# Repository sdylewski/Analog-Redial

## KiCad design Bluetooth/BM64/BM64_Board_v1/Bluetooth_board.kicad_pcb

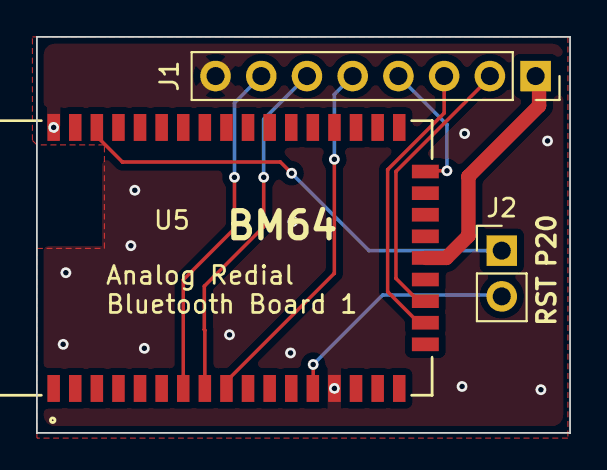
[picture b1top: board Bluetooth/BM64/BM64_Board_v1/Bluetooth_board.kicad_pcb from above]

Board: 2 copper layers, 29.6 x 22.0 mm, 3 parts (0 on the bottom side), 10 nets.

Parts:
J1: PINHD_1x8_Female; PinSocket_1x08_P2.54mm_Vertical
J2: PINHD_1x4_Male; PinHeader_1x02_P2.54mm_Vertical
U5: BM64SPKS1MC2-0003AA; BM64_MCH

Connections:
+3.3V: J1.1, U5.22 (BAT_IN)
/A0HPL: J1.7, U5.7 (AOHPL)
/Mic_N1: J1.6, U5.8 (MIC_N1)
/Mic_P1: J1.5, U5.9 (MIC_P1)
/RST: J2.2, U5.13 (RST_N)
/espUartRx: J1.2, U5.20 (HCI_TXD)
/espUartTx: J1.3, U5.19 (HCI_RXD)
GND: J1.8, U5.14 (GND), U5.43 (GND)
unnamed: J1.4, U5.26 (MFB)
unnamed: J2.1, U5.41 (P2_0)

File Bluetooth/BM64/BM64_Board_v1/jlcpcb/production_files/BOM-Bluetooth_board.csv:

Comment,Designator,Footprint,LCSC,Quantity
BM64SPKS1MC2-0003AA,U5,BM64_MCH,,1
PINHD_1x8_Female,J1,PinSocket_1x08_P2.54mm_Vertical,,1
PINHD_1x4_Male,J2,PinHeader_1x02_P2.54mm_Vertical,,1

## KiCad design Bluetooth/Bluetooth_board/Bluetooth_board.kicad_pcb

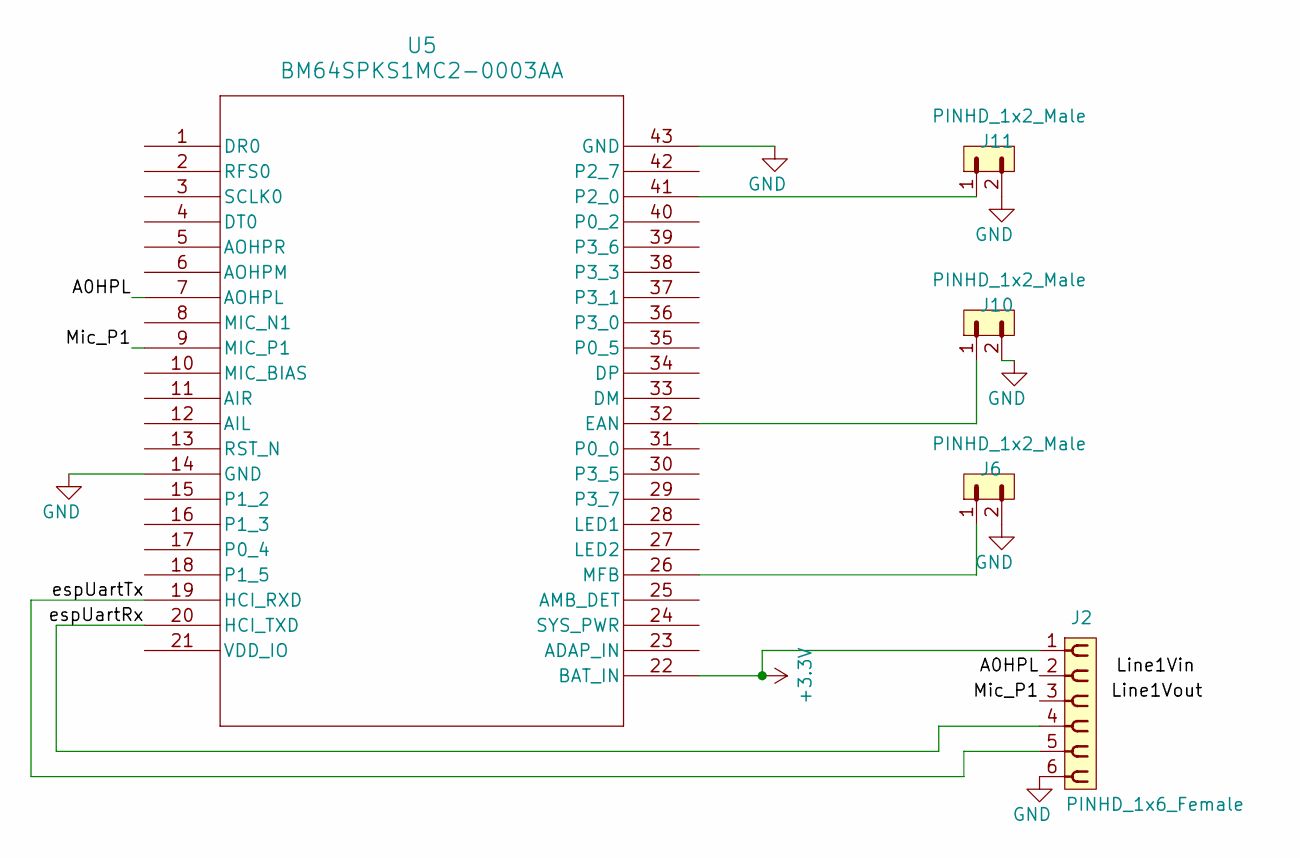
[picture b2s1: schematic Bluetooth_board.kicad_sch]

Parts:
J2: PINHD_1x6_Female; PinSocket_1x06_P2.54mm_Vertical
J6, J10, J11: PINHD_1x2_Male; PinHeader_1x02_P2.54mm_Vertical
U5: BM64SPKS1MC2-0003AA; BM64_MCH

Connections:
+3.3V: J2.1, U5.22 (BAT_IN)
/A0HPL: J2.2, U5.7 (AOHPL)
/Mic_P1: J2.3, U5.9 (MIC_P1)
/espUartRx: J2.4, U5.20 (HCI_TXD)
/espUartTx: J2.5, U5.19 (HCI_RXD)
GND: J2.6, J6.2, J10.2, J11.2, U5.14 (GND), U5.43 (GND)
unnamed: J10.1, U5.32 (EAN)
unnamed: J6.1, U5.26 (MFB)
unnamed: J11.1, U5.41 (P2_0)

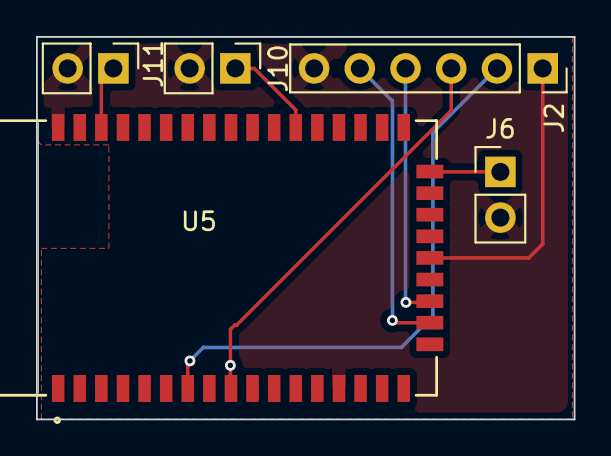
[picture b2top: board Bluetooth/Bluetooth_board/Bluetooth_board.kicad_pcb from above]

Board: 2 copper layers, 29.9 x 21.2 mm, 5 parts (0 on the bottom side), 9 nets.

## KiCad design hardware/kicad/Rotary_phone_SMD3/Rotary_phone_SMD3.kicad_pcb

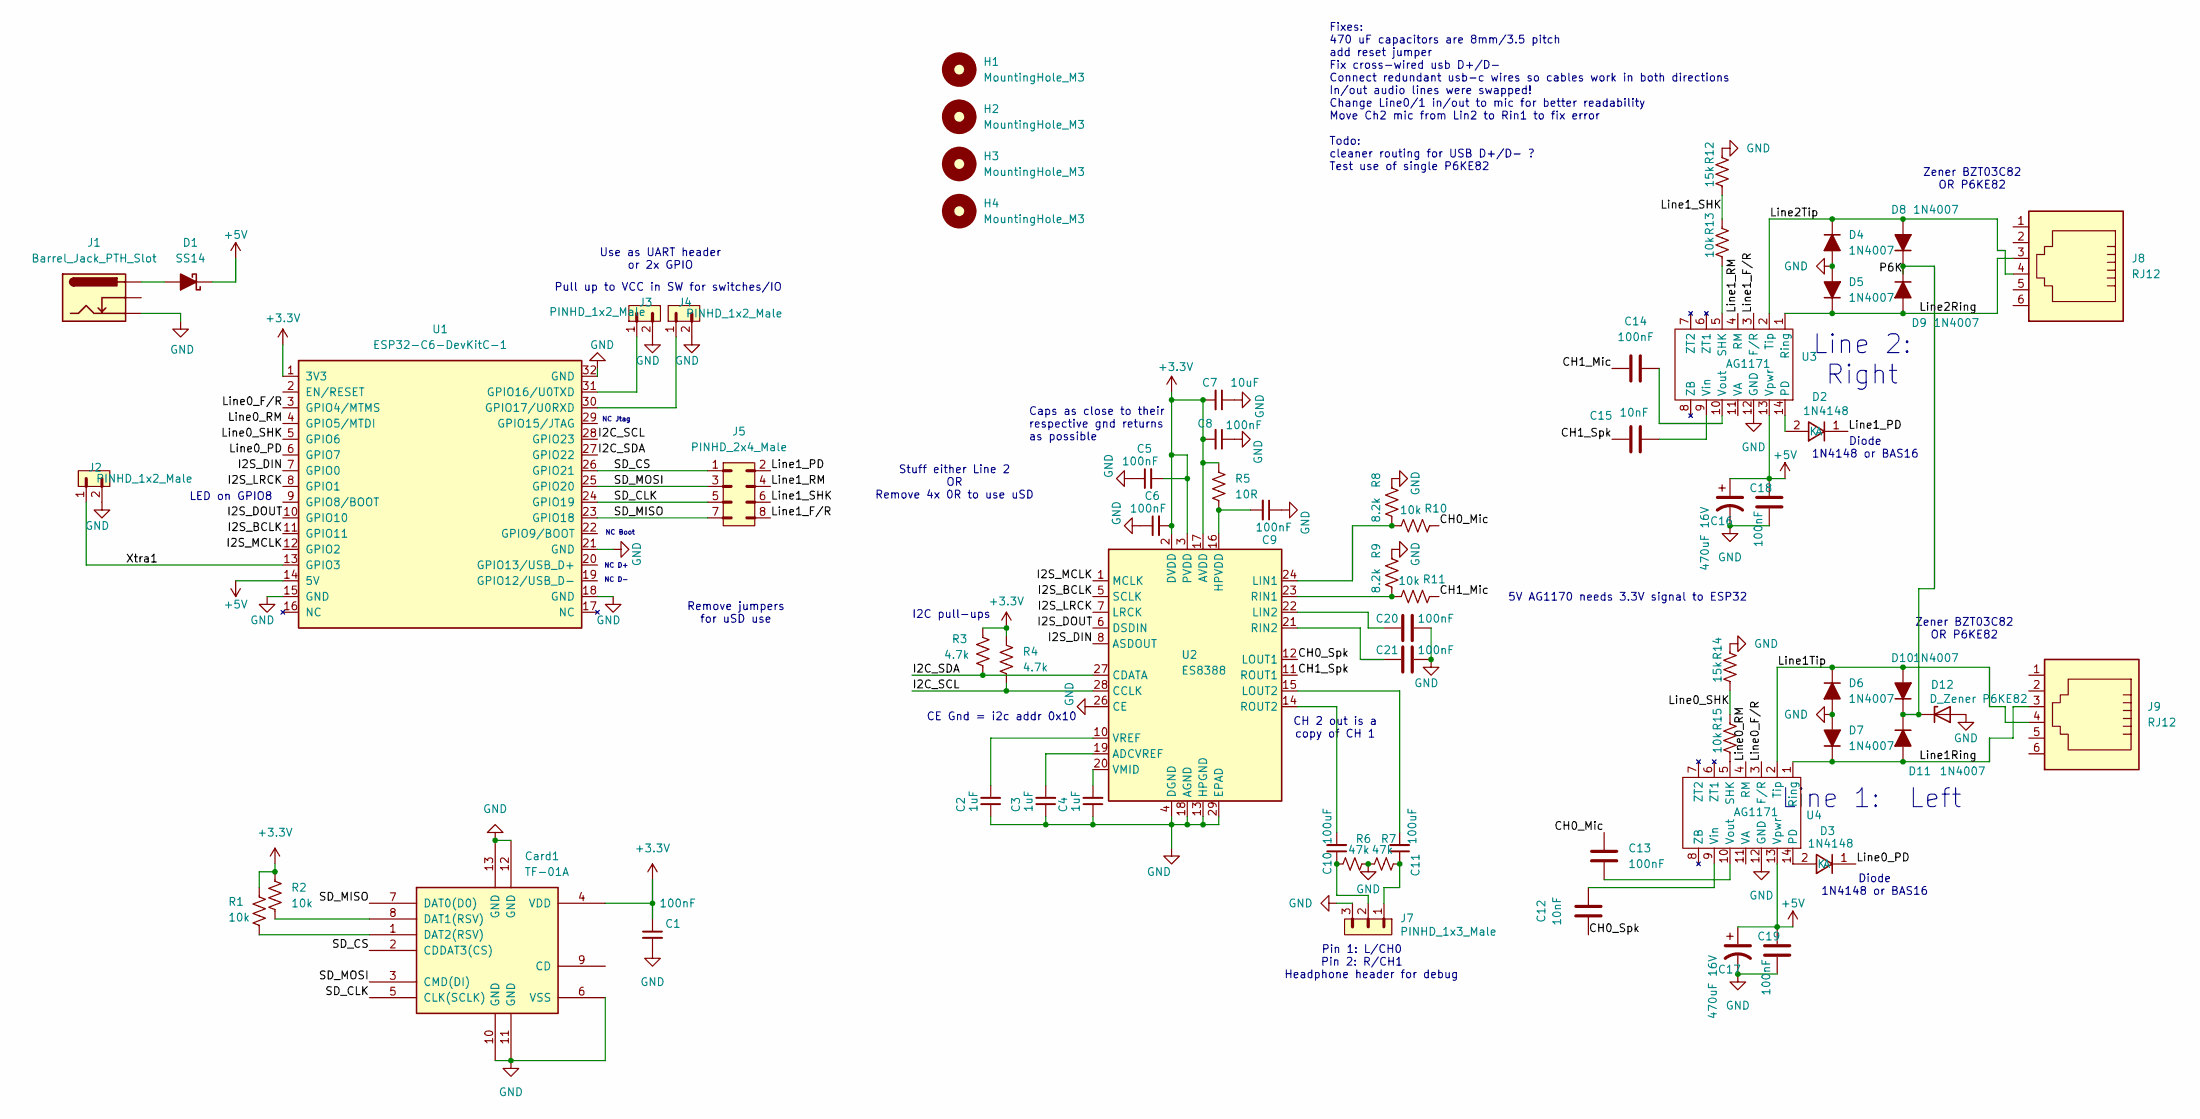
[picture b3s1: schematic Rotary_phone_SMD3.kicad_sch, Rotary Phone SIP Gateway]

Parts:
C1, C5, C6, C8, C9: 100nF; C_0402_1005Metric; Voltage 1kV; Tolerance 100%
C2, C3, C4: 1uF; C_0402_1005Metric; Voltage 1kV; Tolerance 100%
C7: 10uF; C_0402_1005Metric; Voltage 1kV; Tolerance 100%
C10, C11: 100uF; C_1206_3216Metric; Voltage 1kV; Tolerance 100%
C12, C15: 10nF; C_0402_1005Metric
C13, C14, C18, C19, C20, C21: 100nF; C_0402_1005Metric
C16, C17: 470uF 16V; CP_Radial_D8.0mm_P3.50mm
Card1: TF-01A; Manufacturer Part TF-01A; LCSC C91145
D1: SS14; D_SMA
D2, D3: 1N4148; 1N4148W_C81598; Manufacturer Part 1N4148W; LCSC C81598
D4, D5, D6, D7, D8, D9, D10, D11: 1N4007; 1N4007W_C18199088
D12: D_Zener P6KE82; D_DO-41_SOD81_P10.16mm_Horizontal
H1, H2, H3, H4: MountingHole_M3; MountingHole_3.2mm_M3
J1: Barrel_Jack_PTH_Slot
J2, J3, J4: PINHD_1x2_Male; PinHeader_1x02_P2.54mm_Vertical
J5: PINHD_2x4_Male; PinHeader_2x04_P2.54mm_Vertical
J7: PINHD_1x3_Male; PinHeader_1x03_P2.54mm_Vertical
J8, J9: RJ12; RJ12_Amphenol_87180_Horizontal
R1, R2, R10, R11, R13, R15: 10k; R_0402_1005Metric
R3, R4: 4.7k; R_0402_1005Metric
R5: 10R; R_0402_1005Metric
R6, R7: 47k; R_0402_1005Metric
R8, R9: 8.2k; R_0402_1005Metric
R12, R14: 15k; R_0402_1005Metric
U1: ESP32-C6-DevKitC-1
U2: ES8388; QFN-28-1EP_4x4mm_P0.45mm_EP2.6x2.6mm
U3, U4: AG1171; AG1171_SIL

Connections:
+3.3V: C1.1, C5.2, C6.2, C7.2, C8.2, Card1.4 (VDD), R1.2, R2.1, R3.1, R4.1, R5.1, U1.1 (3V3), U2.2 (DVDD), U2.3 (PVDD), U2.17 (AVDD)
+5V: C16.1, C17.1, C18.1, C19.1, D1.1 (K), U1.14 (5V), U3.13 (Vpwr), U4.13 (Vpwr)
/CH0_Mic: C13.1, R10.1
/CH0_Spk: C12.1, U2.12 (LOUT1)
/CH1_Mic: C14.2, R11.1
/CH1_Spk: C15.2, U2.11 (ROUT1)
/I2C_SCL: R4.2, U1.28 (GPIO23), U2.28 (CCLK)
/I2C_SDA: R3.2, U1.27 (GPIO22), U2.27 (CDATA)
/I2S_BCLK: U1.11 (GPIO11), U2.5 (SCLK)
/I2S_DIN: U1.7 (GPIO0), U2.8 (ASDOUT)
/I2S_DOUT: U1.10 (GPIO10), U2.6 (DSDIN)
/I2S_LRCK: U1.8 (GPIO1), U2.7 (LRCK)
/I2S_MCLK: U1.12 (GPIO2), U2.1 (MCLK)
/Line0_F/R: U1.3 (GPIO4/MTMS), U4.3 (F/R)
/Line0_PD: D3.1 (K), U1.6 (GPIO7)
/Line0_RM: U1.4 (GPIO5/MTDI), U4.4 (RM)
/Line0_SHK: R14.2, R15.1, U1.5 (GPIO6)
/Line1Ring: D7.1 (K), D11.2 (A), J9.3, U4.1 (Ring)
/Line1Tip: D6.1 (K), D10.2 (A), J9.4, U4.2 (Tip)
/Line1_F/R: J5.8, U3.3 (F/R)
/Line1_PD: D2.1 (K), J5.2
/Line1_RM: J5.4, U3.4 (RM)
/Line1_SHK: J5.6, R12.2, R13.1
/Line2Ring: D5.1 (K), D9.2 (A), J8.3, U3.1 (Ring)
/Line2Tip: D4.1 (K), D8.2 (A), J8.4, U3.2 (Tip)
/P6K: D8.1 (K), D9.1 (K), D10.1 (K), D11.1 (K), D12.1 (K)
/SD_CLK: Card1.5 (CLK(SCLK)), J5.5, U1.24 (GPIO19)
/SD_CS: Card1.2 (CDDAT3(CS)), J5.1, U1.26 (GPIO21)
/SD_MISO: Card1.7 (DAT0(D0)), J5.7, U1.23 (GPIO18)
/SD_MOSI: Card1.3 (CMD(DI)), J5.3, U1.25 (GPIO20)
/Xtra1: J2.1, U1.13 (GPIO3)
GND: C1.2, C2.1, C3.1, C4.1, C5.1, C6.1, C7.1, C8.1, C9.1, C16.2, C17.2, C18.2, C19.2, C20.1, C21.1, Card1.6 (VSS), Card1.10 (GND), Card1.11 (GND), Card1.12 (GND), Card1.13 (GND), D4.2 (A), D5.2 (A), D6.2 (A), D7.2 (A), D12.2 (A), J1.GND, J2.2, J3.2, J4.2, J7.3, R6.1, R7.2, R8.1, R9.1, R12.1, R14.1, U1.15 (GND), U1.18 (GND), U1.21 (GND), U1.32 (GND), U2.4 (DGND), U2.13 (HPGND), U2.18 (AGND), U2.26 (CE), U2.29 (EPAD), U3.12 (GND), U4.12 (GND)
unnamed: C10.1, J7.2, R6.2
unnamed: C11.1, J7.1, R7.1
unnamed: Card1.8 (DAT1(RSV)), R2.2
unnamed: Card1.1 (DAT2(RSV)), R1.1
unnamed: D1.2 (A), J1.PWR
unnamed: D2.2 (A), U3.14 (PD)
unnamed: D3.2 (A), U4.14 (PD)
unnamed: J3.1, U1.31 (GPIO16/U0TXD)
unnamed: J4.1, U1.30 (GPIO17/U0RXD)
unnamed: C3.2, U2.19 (ADCVREF)
unnamed: C9.2, R5.2, U2.16 (HPVDD)
unnamed: R8.2, R10.2, U2.24 (LIN1)
unnamed: C20.2, U2.22 (LIN2)
unnamed: C11.2, U2.15 (LOUT2)
unnamed: R9.2, R11.2, U2.23 (RIN1)
unnamed: C21.2, U2.21 (RIN2)
unnamed: C10.2, U2.14 (ROUT2)
unnamed: C4.2, U2.20 (VMID)
unnamed: C2.2, U2.10 (VREF)
unnamed: R13.2, U3.5 (SHK)
unnamed: C15.1, U3.9 (Vin)
unnamed: C14.1, U3.10 (Vout)
unnamed: R15.2, U4.5 (SHK)
unnamed: C12.2, U4.9 (Vin)
unnamed: C13.2, U4.10 (Vout)

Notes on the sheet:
Caps as close to their respective gnd returns as possible
LED on GPIO8
NC D-
Stuff either Line 2 OR Remove 4x 0R to use uSD
Pin 1: L/CH0 Pin 2: R/CH1
Diode 1N4148 or BAS16
NC Boot
Pull up to VCC in SW for switches/IO
CE Gnd = i2c addr 0x10
Remove jumpers for uSD use
Line 2: Right
NC Jtag
I2C pull-ups
Zener BZT03C82 OR P6KE82
Use as UART header or 2x GPIO
CH 2 out is a copy of CH 1
Line 1: Left
5V AG1170 needs 3.3V signal to ESP32
NC D+
Headphone header for debug
Fixes: 470 uF capacitors are 8mm/3.5 pitch add reset jumper Fix cross-wired usb D+/D- Connect redundant usb-c wires so cables work in both directions In/out audio lines were swapped! Change Line0/1 in/out to mic for better readability Move Ch2 mic from Lin2 to Rin1 to fix error Todo: cleaner routin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

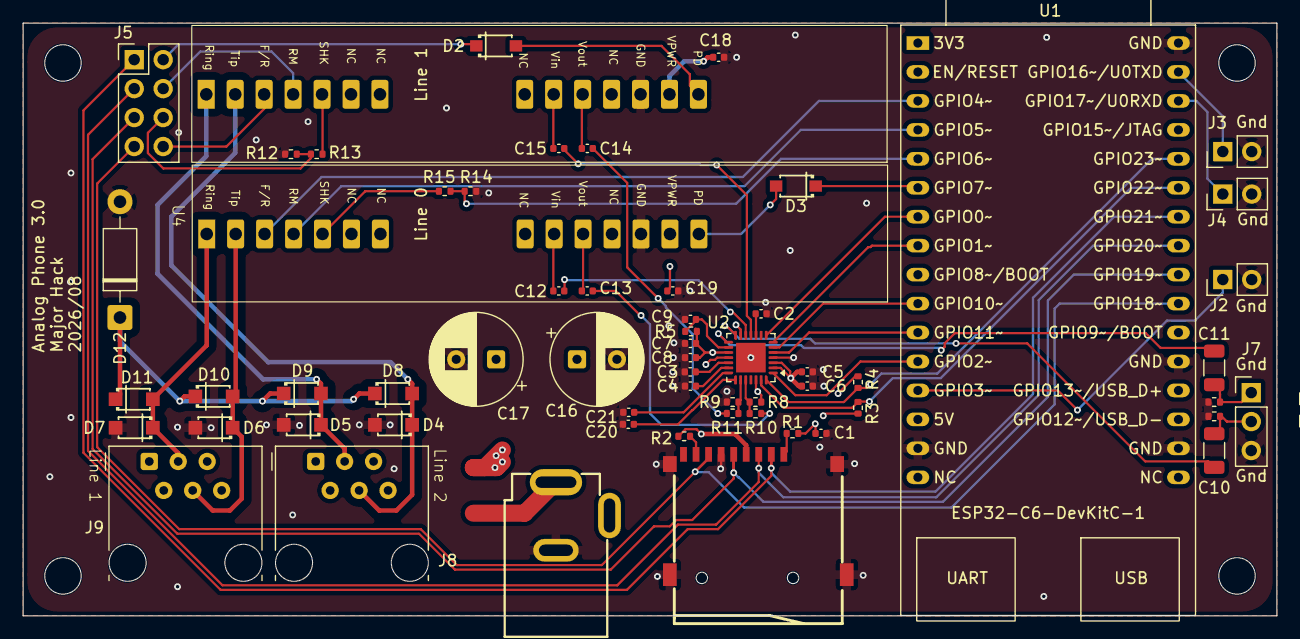
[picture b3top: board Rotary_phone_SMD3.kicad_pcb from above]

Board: 4 copper layers, 110.0 x 52.0 mm, 64 parts (0 on the bottom side), 56 nets.

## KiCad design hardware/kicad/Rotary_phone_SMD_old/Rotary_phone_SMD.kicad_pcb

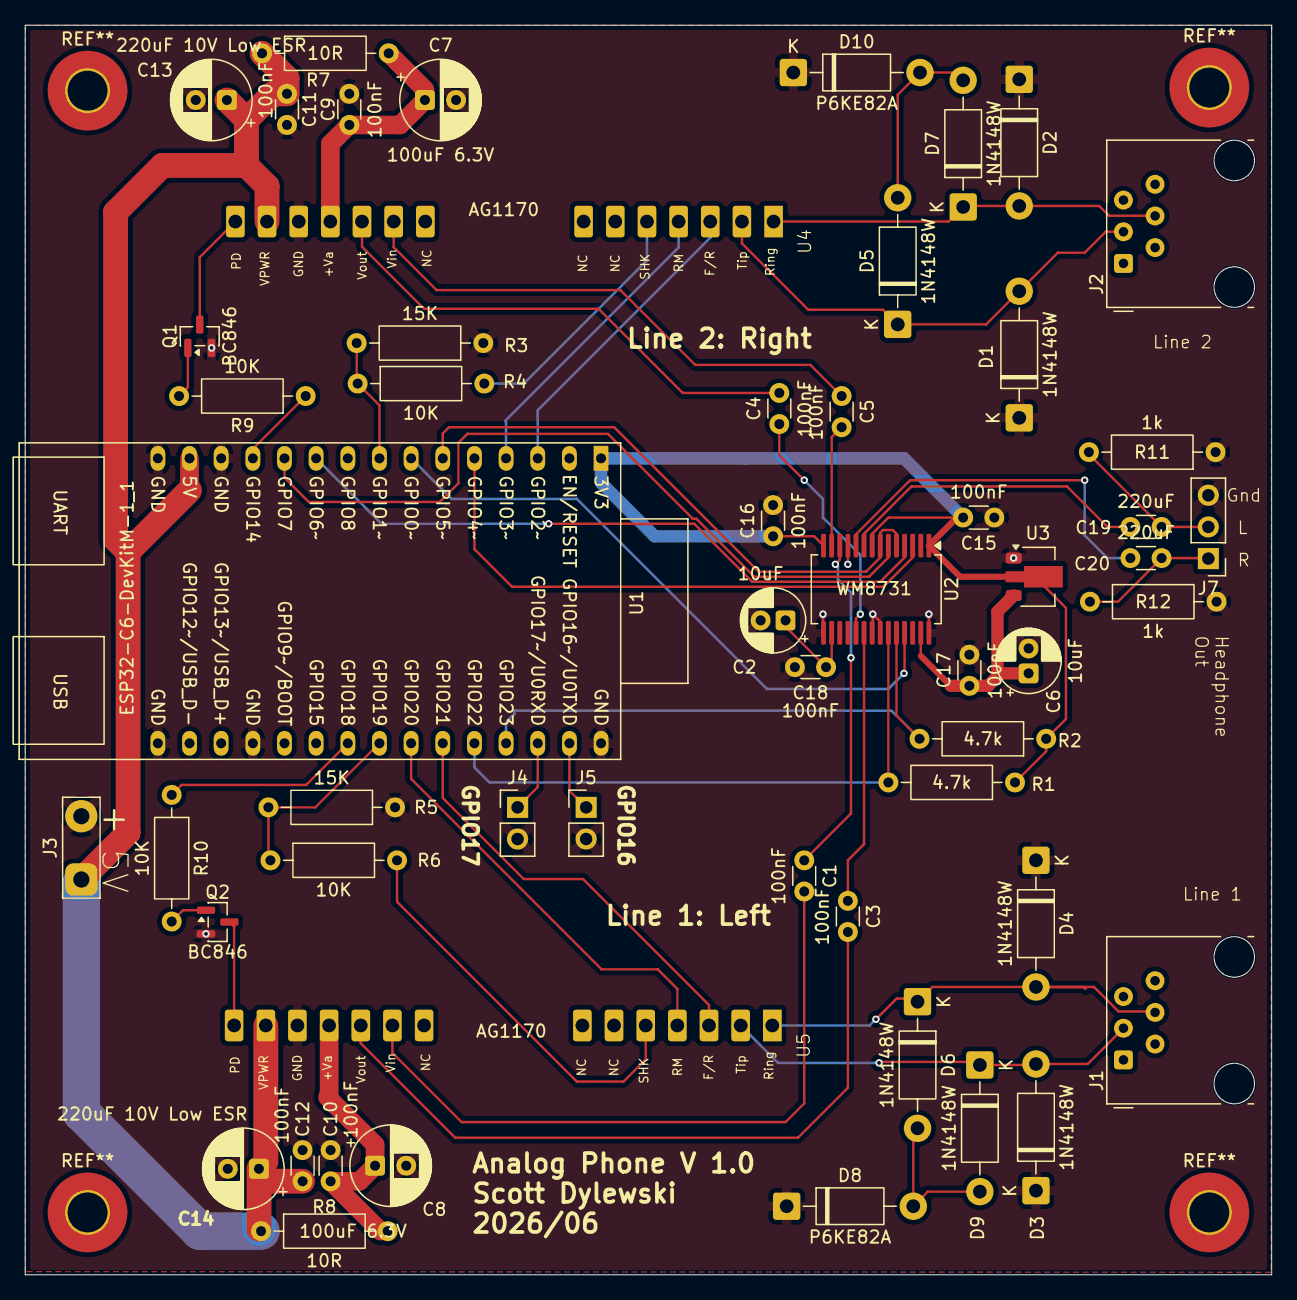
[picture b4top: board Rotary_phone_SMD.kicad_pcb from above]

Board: 2 copper layers, 100.0 x 100.2 mm, 55 parts (0 on the bottom side), 48 nets.

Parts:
C1, C3, C4, C5, C9, C10, C11, C12, C15, C16, C17, C18: 100nF; C_0402_1005Metric
C2, C6: 10uF; C_0603_1608Metric
C7, C8: 100uF 6.3V; CP_Elec_6.3x7.7
C13, C14: 220uF 10V Low ESR; CP_Elec_8x10.5
C19, C20: 220uF; CP_Elec_8x10.5
D1, D2, D3, D4, D5, D6, D7, D9: 1N4148W; D_SOD-123
D8, D10: P6KE82A; D_SOD-123
J1, J2: RJ12; RJ12_Amphenol_54601-x06_Horizontal
J3: Conn_01x02_Pin; TestPoint_2Pads_Pitch5.08mm_Drill1.3mm
J4, J5: PINHD_1x2_Male; PinHeader_1x02_P2.54mm_Vertical
J7: PINHD_1x3_Male; PinHeader_1x03_P2.54mm_Vertical
Q1, Q2: BC846; SOT-23
R1, R2: 4.7k; R_0402_1005Metric
R3, R5: 15K; R_0402_1005Metric
R4, R6, R9, R10: 10K; R_0402_1005Metric
R7, R8: 10R; R_0402_1005Metric
R11, R12: 1k; R_0402_1005Metric
U1: ESP32-C6-DevKitM-1_1; ESP32-C6-DevKitM-1
U2: WM8731; WM8731_SSOP-28
U3: MCP1700x-180xxMB; SOT-89-3
U4, U5: AG1170; AG1170_SIL

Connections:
+3.3V: C15.2, C16.1, R1.1, R2.1, U1.1 (3V3), U2.1 (DBVDD), U2.8 (HPVDD), U2.14 (AVDD), U3.2 (VI)
+5V: C11.1, C12.1, C13.1, C14.1, J3.1, R7.1, R8.1, U1.14 (5V), U4.13 (Vpwr), U5.13 (Vpwr)
/I2C_SCL: R2.2, U1.27 (GPIO23), U2.24 (SCLK)
/I2C_SDA: R1.2, U1.26 (GPIO22), U2.23 (SDIN)
/I2S_BCLK: U1.5 (GPIO4/MTMS), U2.3 (BCLK)
/I2S_DIN: U1.11 (GPIO7), U2.6 (ADCDAT)
/I2S_DOUT: U1.10 (GPIO6), U2.4 (DACDAT)
/I2S_LRCK: U1.6 (GPIO5/MTDI), U2.5 (DACLRC), U2.7 (ADCLRC)
/I2S_MCLK: U1.7 (GPIO0), U2.25 (XTI/MCLK)
/Line1_F/R: U1.25 (GPIO21), U5.3 (F/R)
/Line1_PD: R10.1, U1.22 (GPIO18)
/Line1_RM: U1.24 (GPIO20), U5.4 (RM)
/Line1_SHK: R5.2, R6.1, U1.23 (GPIO19)
/Line2_F/R: U1.3 (GPIO2), U4.3 (F/R)
/Line2_PD: R9.1, U1.12 (GPIO14)
/Line2_RM: U1.4 (GPIO3), U4.4 (RM)
/Line2_SHK: R3.2, R4.1, U1.8 (GPIO1)
GND: C2.2, C6.2, C7.2, C8.2, C9.2, C10.2, C11.2, C12.2, C13.2, C14.2, C15.1, C16.2, C17.2, C18.2, D1.1 (K), D2.1 (K), D3.1 (K), D4.1 (K), D8.1 (K), D10.1 (K), J3.2, J4.2, J5.2, J7.3, Q1.2 (E), Q2.2 (E), R3.1, R5.1, R11.1, R12.2, U1.13 (GND), U1.15 (GND), U1.16 (GND), U1.19 (GND), U1.30 (GND), U2.11 (HPGND), U2.15 (AGND), U2.21 (MODE), U2.22 (CSB), U2.28 (DGND), U3.1 (GND), U4.12 (GND), U5.12 (GND)
unnamed: C19.1, J7.2, R11.2
unnamed: C20.1, J7.1, R12.1
unnamed: D1.2 (A), D5.1 (K), J2.3, U4.2 (Tip)
unnamed: D2.2 (A), D7.1 (K), J2.4, U4.1 (Ring)
unnamed: D3.2 (A), D9.1 (K), J1.3, U5.2 (Tip)
unnamed: D4.2 (A), D6.1 (K), J1.4, U5.1 (Ring)
unnamed: D6.2 (A), D8.2 (A), D9.2 (A)
unnamed: D5.2 (A), D7.2 (A), D10.2 (A)
unnamed: Q1.1 (B), R9.2
unnamed: Q1.3 (C), U4.14 (PD)
unnamed: Q2.1 (B), R10.2
unnamed: Q2.3 (C), U5.14 (PD)
unnamed: J5.1, U1.29 (GPIO16/U0TXD)
unnamed: J4.1, U1.28 (GPIO17/U0RXD)
unnamed: C6.1, C17.1, U2.27 (DCVDD), U3.3 (VO)
unnamed: C19.2, U2.9 (LHPOUT)
unnamed: C3.1, U2.20 (LLINEIN)
unnamed: C1.1, U2.12 (LOUT)
unnamed: C20.2, U2.10 (RHPOUT)
unnamed: C4.1, U2.19 (RLINEIN)
unnamed: C5.2, U2.13 (ROUT)
unnamed: C2.1, C18.1, U2.16 (VMID)
unnamed: R4.2, U4.5 (SHK)
unnamed: C7.1, C9.1, R7.2, U4.11 (VA)
unnamed: C5.1, U4.9 (Vin)
unnamed: C4.2, U4.10 (Vout)
unnamed: R6.2, U5.5 (SHK)
unnamed: C8.1, C10.1, R8.2, U5.11 (VA)
unnamed: C1.2, U5.9 (Vin)
unnamed: C3.2, U5.10 (Vout)
